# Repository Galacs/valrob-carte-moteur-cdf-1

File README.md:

# Carte moteur CDF 1

ESP32-S3-WROOM-1 Dual 5A DC motor driver

## IC List

- ESP32-S3-WROOM-1 (Main MCU Module)
- AP2112K (MCU 3v3 LDO)
- DRV8874 (Integrated FETs H-bridge)

## Top preview

## Preview 3d render

## Pin definitions

```c
#define EN_1_PIN 2
#define PH_1_PIN 3
#define SLEEP_1_PIN 5
#define FAULT_1_PIN 6
#define IPROPRI_1_PIN 7

#define EN_2_PIN 14
#define PH_2_PIN 17
#define SLEEP_2_PIN 21
#define FAULT_2_PIN 38
#define IPROPRI_2_PIN 18

#define SPI_CS_0_PIN 10
#define SPI_CS_1_PIN 8
#define SPI_MOSI_PIN 11
#define SPI_MISO_PIN 13
#define SPI_SCLK_PIN 12

#define ALERT_1_PIN 47
#define ALERT_2_PIN 48

#define BATT_SENSE_PIN 9
```

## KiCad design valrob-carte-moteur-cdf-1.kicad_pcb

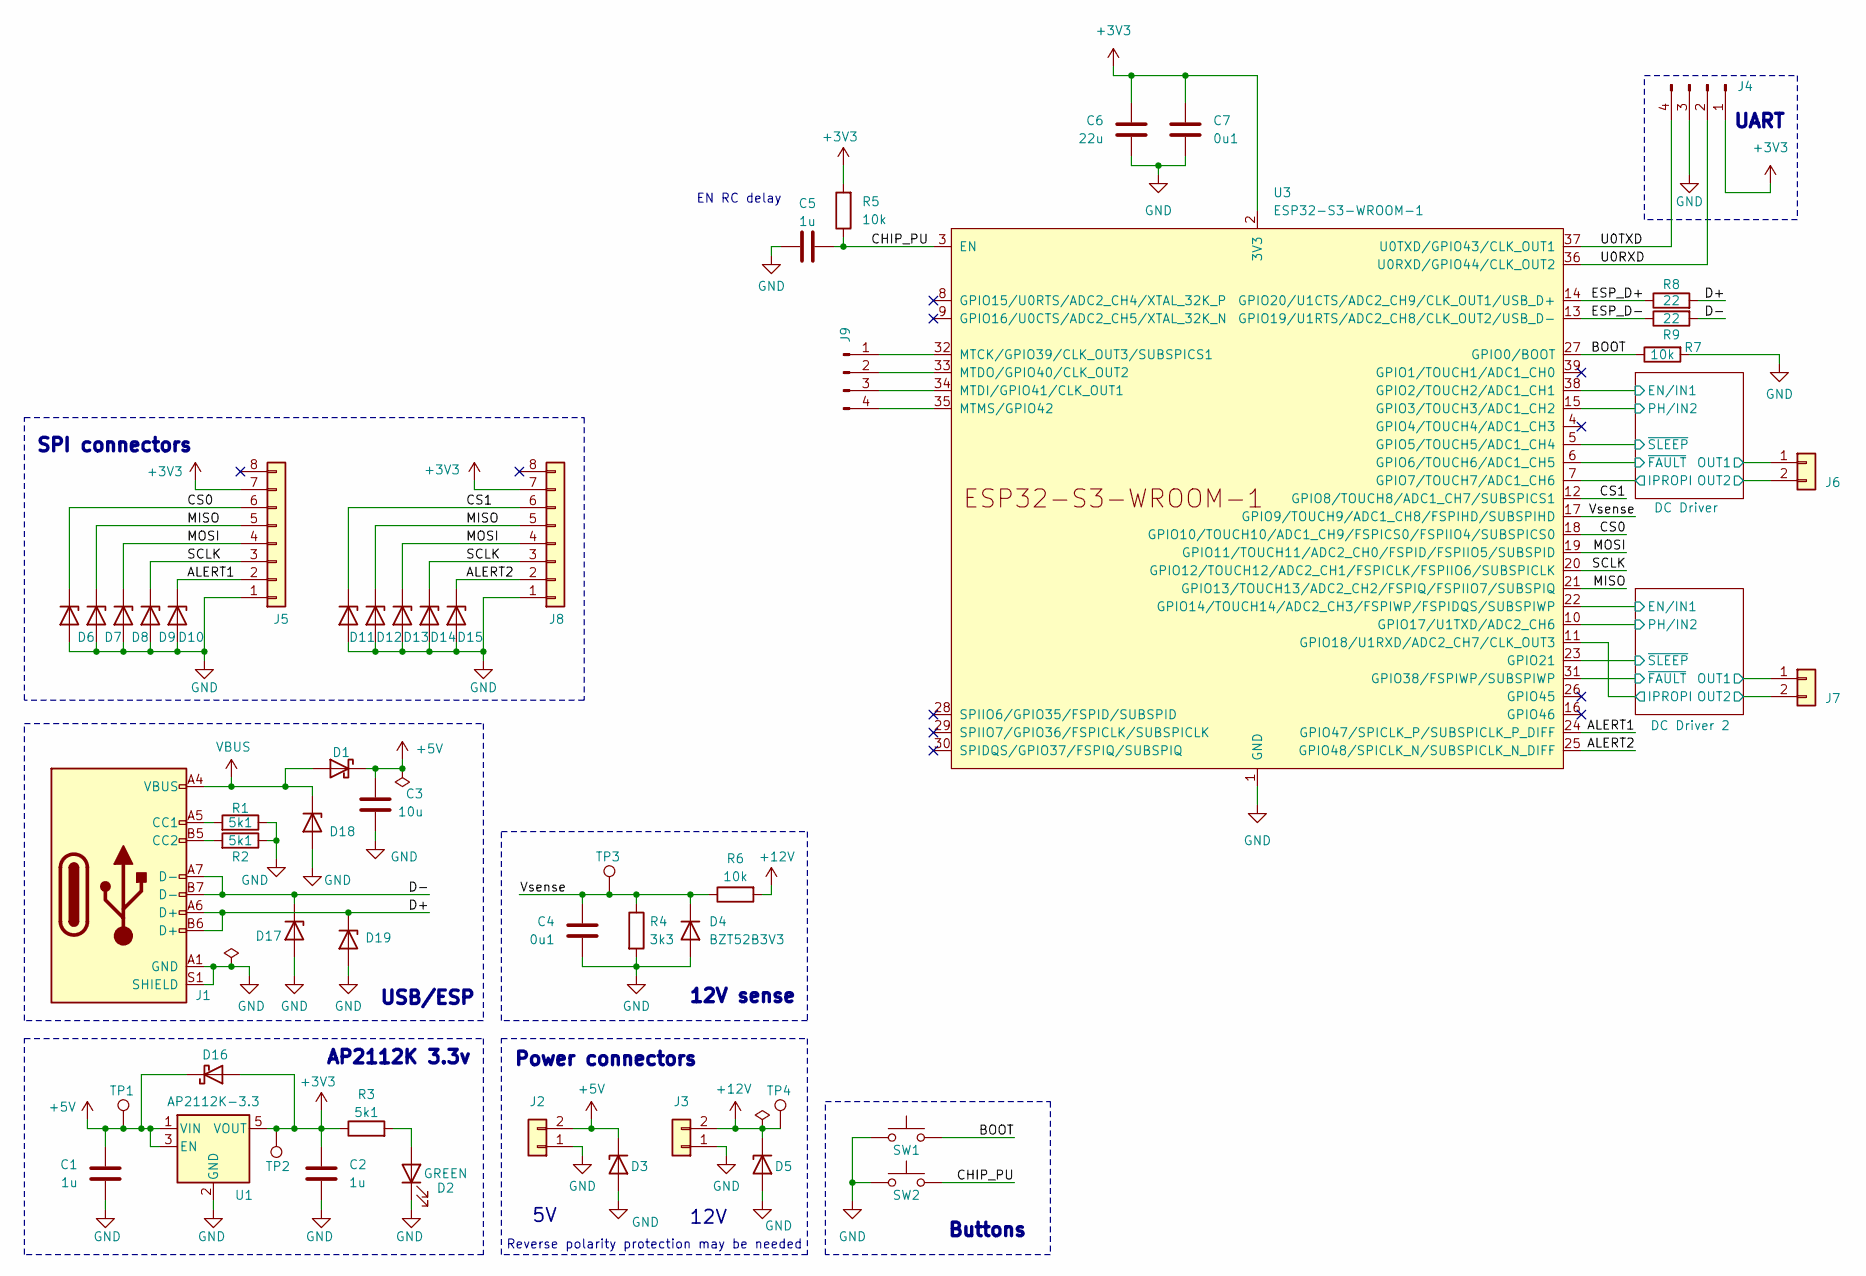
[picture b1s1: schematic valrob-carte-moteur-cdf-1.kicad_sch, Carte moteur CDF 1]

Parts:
C1, C2, C5: 1u; C_0603_1608Metric; Manufacturer Part Number CL10A105KB8NNNC; JLCPCB Part # C15849
C3: 10u; C_0603_1608Metric; Manufacturer Part Number CL10A106KP8NNNC; JLCPCB Part # C19702
C4, C7: 0u1; C_0603_1608Metric; Manufacturer Part Number CC0603KRX7R9BB104; JLCPCB Part # C14663
C6: 22u; C_0805_2012Metric; Manufacturer Part Number CL21A226MAQNNNE; JLCPCB Part # C45783
D1, D16: D_Schottky; D_SMA; Manufacturer Part Number SS54; JLCPCB Part # C22452
D2: GREEN; LED_0805_2012Metric; Manufacturer Part Number KT-0805G; JLCPCB Part # C2297
D3: P6SMB6.8CA/TR13; D_SMB; Manufacturer Part Number P6SMB6.8CA/TR13; JLCPCB Part # C78395
D4: BZT52B3V3; D_SOD-123; Manufacturer Part Number BZT52B3V3; JLCPCB Part # C19077392
D5: SMAJ12A; D_SMA; Manufacturer Part Number SMAJ12A; JLCPCB Part # C19077531
D6, D7, D8, D9, D10, D11, D12, D13, D14, D15, D17, D18, D19: H5VU10U; Diode_DFN1006; Manufacturer Part Number H5VU10U; JLCPCB Part # C22395519
J1: USB_C_Receptacle_USB2.0_14P; USB_C_Receptacle_HRO_TYPE-C-31-M-12; Manufacturer Part Number TYPE-C16PIN; JLCPCB Part # C393939
J2, J3, J6, J7: Conn_01x02; JST_XH_S2B-XH-A_1x02_P2.50mm_Horizontal
J4, J9: Conn_01x04_Pin; PinHeader_1x04_P2.54mm_Vertical
J5, J8: Conn_01x08; Molex_PicoBlade_53048-0810_1x08_P1.25mm_Horizontal
R1, R2, R3: 5k1; R_0603_1608Metric; Manufacturer Part Number 0603WAF5101T5E; JLCPCB Part # C23186
R4: 3k3; R_0603_1608Metric; Manufacturer Part Number 0603WAF3301T5E; JLCPCB Part # C22978
R5, R6, R7: 10k; R_0603_1608Metric; Manufacturer Part Number 0603WAF1002T5E; JLCPCB Part # C25804
R8, R9: 22; R_0603_1608Metric; Manufacturer Part Number 0603WAF220JT5E; JLCPCB Part # C23345
SW1, SW2: SW_Push; SW_SPST_TS-1088-xR020; Manufacturer Part Number TS-1088-AR02016; JLCPCB Part # C720477
TP1, TP2, TP3, TP4: TestPoint; TestPoint_Pad_D2.0mm
U1: AP2112K-3.3; SOT-23-5; Manufacturer Part Number AP2112K-3.3TRG1; JLCPCB Part # C51118
U3: ESP32-S3-WROOM-1

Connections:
+3V3: C2.1, C6.1, C7.1, D16.2 (A), J4.1, J5.7, J8.7, R3.1, R5.2, TP2.1, U1.5 (VOUT), U3.2 (3V3); also elsewhere on the board
+5V: C1.1, C3.1, D1.1 (K), D3.1 (K), D16.1 (K), J2.2, TP1.1, U1.1 (VIN), U1.3 (EN)
+12V: D5.1 (K), J3.2, R6.2, TP4.1; also elsewhere on the board
/ALERT1: D10.1 (K), J5.2, U3.24 (GPIO47/SPICLK_P/SUBSPICLK_P_DIFF)
/ALERT2: D15.1 (K), J8.2, U3.25 (GPIO48/SPICLK_N/SUBSPICLK_N_DIFF)
/BOOT: R7.1, SW1.2, U3.27 (GPIO0/BOOT)
/CHIP_PU: C5.2, R5.1, SW2.2, U3.3 (EN)
/CS0: D6.1 (K), J5.6, U3.18 (GPIO10/TOUCH10/ADC1_CH9/FSPICS0/FSPIIO4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)
/CS1: D11.1 (K), J8.6, U3.12 (GPIO8/TOUCH8/ADC1_CH7/SUBSPICS1)
/D+: D19.1 (K), J1.A6 (D+), J1.B6 (D+), R8.2
/D-: D17.1 (K), J1.A7 (D-), J1.B7 (D-), R9.2
/DC Driver 2/EN/IN1: U3.22 (GPIO14/TOUCH14/ADC2_CH3/FSPIWP/FSPIDQS/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); also elsewhere on the board
/DC Driver 2/IPROPI: U3.11 (GPIO18/U1RXD/ADC2_CH7/CLK_OUT3); also elsewhere on the board
/DC Driver 2/OUT1: J7.1; also elsewhere on the board
/DC Driver 2/OUT2: J7.2; also elsewhere on the board
/DC Driver 2/PH/IN2: U3.10 (GPIO17/U1TXD/ADC2_CH6); also elsewhere on the board
/DC Driver 2/~FAULT: U3.31 (GPIO38/FSPIWP/SUBSPIWP); also elsewhere on the board
/DC Driver 2/~SLEEP: U3.23 (GPIO21); also elsewhere on the board
/DC Driver/EN/IN1: U3.38 (GPIO2/TOUCH2/ADC1_CH1); also elsewhere on the board
/DC Driver/IPROPI: U3.7 (GPIO7/TOUCH7/ADC1_CH6); also elsewhere on the board
/DC Driver/OUT1: J6.1; also elsewhere on the board
/DC Driver/OUT2: J6.2; also elsewhere on the board
/DC Driver/PH/IN2: U3.15 (GPIO3/TOUCH3/ADC1_CH2); also elsewhere on the board
/DC Driver/~FAULT: U3.6 (GPIO6/TOUCH6/ADC1_CH5); also elsewhere on the board
/DC Driver/~SLEEP: U3.5 (GPIO5/TOUCH5/ADC1_CH4); also elsewhere on the board
/ESP_D+: R8.1, U3.14 (GPIO20/U1CTS/ADC2_CH9/CLK_OUT1/USB_D+)
/ESP_D-: R9.1, U3.13 (GPIO19/U1RTS/ADC2_CH8/CLK_OUT2/USB_D-)
/MISO: D7.1 (K), D12.1 (K), J5.5, J8.5, U3.21 (GPIO13/TOUCH13/ADC2_CH2/FSPIQ/FSPIIO7/S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)
/MOSI: D8.1 (K), D13.1 (K), J5.4, J8.4, U3.19 (GPIO11/TOUCH11/ADC2_CH0/FSPID/FSPIIO5/S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)
/SCLK: D9.1 (K), D14.1 (K), J5.3, J8.3, U3.20 (GPIO12/TOUCH12/ADC2_CH1/FSPICLK/FSPIIO6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)
/U0RXD: J4.2, U3.36 (U0RXD/GPIO44/CLK_OUT2)
/U0TXD: J4.4, U3.37 (U0TXD/GPIO43/CLK_OUT1)
/Vsense: C4.1, D4.1 (K), R4.1, R6.1, TP3.1, U3.17 (GPIO9/TOUCH9/ADC1_CH8/FSPIHD/SUBSPIHD)
GND: C1.2, C2.2, C3.2, C4.2, C5.1, C6.2, C7.2, D2.1 (K), D3.2 (A), D4.2 (A), D5.2 (A), D6.2 (A), D7.2 (A), D8.2 (A), D9.2 (A), D10.2 (A), D11.2 (A), D12.2 (A), D13.2 (A), D14.2 (A), D15.2 (A), D17.2 (A), D18.2 (A), D19.2 (A), J1.A1 (GND), J1.A12 (GND), J1.B1 (GND), J1.B12 (GND), J1.S1 (SHIELD), J2.1, J3.1, J4.3, J5.1, J8.1, R1.1, R2.1, R4.2, R7.2, SW1.1, SW2.1, U1.2 (GND), U3.1 (GND), U3.40 (GND), U3.41 (GND); also elsewhere on the board
unnamed: D2.2 (A), R3.2
unnamed: J1.A5 (CC1), R1.2
unnamed: J1.B5 (CC2), R2.2
unnamed: J9.1, U3.32 (MTCK/GPIO39/CLK_OUT3/SUBSPICS1)
unnamed: J9.2, U3.33 (MTDO/GPIO40/CLK_OUT2)
unnamed: J9.3, U3.34 (MTDI/GPIO41/CLK_OUT1)
unnamed: J9.4, U3.35 (MTMS/GPIO42)
VBUS: D1.2 (A), D18.1 (K), J1.A4 (VBUS), J1.A9 (VBUS), J1.B4 (VBUS), J1.B9 (VBUS)

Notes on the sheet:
SPI connectors
12V sense
Power connectors
Reverse polarity protection may be needed
AP2112K 3.3v
USB/ESP
Buttons
12V
UART
EN RC delay

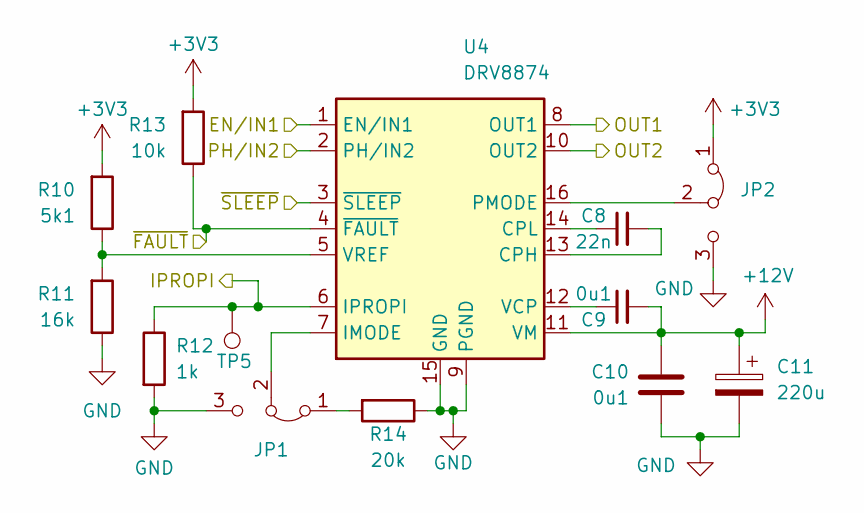
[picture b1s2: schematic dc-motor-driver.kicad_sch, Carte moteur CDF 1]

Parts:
C8: 22n; C_0603_1608Metric; Manufacturer Part Number CL10B223KB8NNNC; JLCPCB Part # C21122
C9, C10: 0u1; C_0603_1608Metric; Manufacturer Part Number CC0603KRX7R9BB104; JLCPCB Part # C14663
C11: 220u; CP_Elec_6.3x7.7; Manufacturer Part Number JVJ35V220M6x8; JLCPCB Part # C46550411
JP1, JP2: Jumper_3_Bridged12; PinHeader_1x03_P2.54mm_Vertical
R10: 5k1; R_0603_1608Metric; Manufacturer Part Number 0603WAF5101T5E; JLCPCB Part # C23186
R11: 16k; R_0805_2012Metric; Manufacturer Part Number 0805W8F1602T5E; JLCPCB Part # C17490
R12: 1k; R_0603_1608Metric; Manufacturer Part Number 0603WAF1001T5E; JLCPCB Part # C21190
R13: 10k; R_0603_1608Metric; Manufacturer Part Number 0603WAF1002T5E; JLCPCB Part # C25804
R14: 20k; R_0603_1608Metric; Manufacturer Part Number 0603WAF2002T5E; JLCPCB Part # C4184
TP5: TestPoint; TestPoint_Pad_D2.0mm
U4: DRV8874; HTSSOP-16-1EP_4.4x5mm_P0.65mm_EP3.4x5mm_Mask2.46x2.31mm_The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; Manufacturer Part Number DRV8874PWPR; JLCPCB Part # C1855818

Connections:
+3V3: JP2.1 (A), R10.2, R13.2; also elsewhere on the board
+12V: C9.2, C10.1, C11.1, U4.11 (VM); also elsewhere on the board
/DC Driver/EN/IN1: U4.1 (EN/IN1); also elsewhere on the board
/DC Driver/IPROPI: R12.1, TP5.1, U4.6 (IPROPI); also elsewhere on the board
/DC Driver/OUT1: U4.8 (OUT1); also elsewhere on the board
/DC Driver/OUT2: U4.10 (OUT2); also elsewhere on the board
/DC Driver/PH/IN2: U4.2 (PH/IN2); also elsewhere on the board
/DC Driver/~FAULT: R13.1, U4.4 (~FAULT); also elsewhere on the board
/DC Driver/~SLEEP: U4.3 (~SLEEP); also elsewhere on the board
GND: C10.2, C11.2, JP1.3 (B), JP2.3 (B), R11.1, R12.2, R14.1, U4.9 (PGND), U4.15 (GND); also elsewhere on the board
unnamed: JP1.1 (A), R14.2
unnamed: JP1.2 (C), U4.7 (IMODE)
unnamed: JP2.2 (C), U4.16 (PMODE)
unnamed: C8.2, U4.13 (CPH)
unnamed: C8.1, U4.14 (CPL)
unnamed: C9.1, U4.12 (VCP)
unnamed: R10.1, R11.2, U4.5 (VREF)

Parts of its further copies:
C12: 22n; C_0603_1608Metric; Manufacturer Part Number CL10B223KB8NNNC; JLCPCB Part # C21122
C13, C14: 0u1; C_0603_1608Metric; Manufacturer Part Number CC0603KRX7R9BB104; JLCPCB Part # C14663
C15: 220u; CP_Elec_6.3x7.7; Manufacturer Part Number JVJ35V220M6x8; JLCPCB Part # C46550411
JP3, JP4: Jumper_3_Bridged12; PinHeader_1x03_P2.54mm_Vertical
R15: 5k1; R_0603_1608Metric; Manufacturer Part Number 0603WAF5101T5E; JLCPCB Part # C23186
R16: 16k; R_0805_2012Metric; Manufacturer Part Number 0805W8F1602T5E; JLCPCB Part # C17490
R17: 1k; R_0603_1608Metric; Manufacturer Part Number 0603WAF1001T5E; JLCPCB Part # C21190
R18: 10k; R_0603_1608Metric; Manufacturer Part Number 0603WAF1002T5E; JLCPCB Part # C25804
R19: 20k; R_0603_1608Metric; Manufacturer Part Number 0603WAF2002T5E; JLCPCB Part # C4184
TP6: TestPoint; TestPoint_Pad_D2.0mm
U5: DRV8874; HTSSOP-16-1EP_4.4x5mm_P0.65mm_EP3.4x5mm_Mask2.46x2.31mm_The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; Manufacturer Part Number DRV8874PWPR; JLCPCB Part # C1855818

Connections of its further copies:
+3V3: JP4.1 (A), R15.2, R18.2; also elsewhere on the board
+12V: C13.2, C14.1, C15.1, U5.11 (VM); also elsewhere on the board
/DC Driver 2/EN/IN1: U5.1 (EN/IN1); also elsewhere on the board
/DC Driver 2/IPROPI: R17.1, TP6.1, U5.6 (IPROPI); also elsewhere on the board
/DC Driver 2/OUT1: U5.8 (OUT1); also elsewhere on the board
/DC Driver 2/OUT2: U5.10 (OUT2); also elsewhere on the board
/DC Driver 2/PH/IN2: U5.2 (PH/IN2); also elsewhere on the board
/DC Driver 2/~FAULT: R18.1, U5.4 (~FAULT); also elsewhere on the board
/DC Driver 2/~SLEEP: U5.3 (~SLEEP); also elsewhere on the board
GND: C14.2, C15.2, JP3.3 (B), JP4.3 (B), R16.1, R17.2, R19.1, U5.9 (PGND), U5.15 (GND); also elsewhere on the board
unnamed: JP3.1 (A), R19.2
unnamed: JP3.2 (C), U5.7 (IMODE)
unnamed: JP4.2 (C), U5.16 (PMODE)
unnamed: C12.2, U5.13 (CPH)
unnamed: C12.1, U5.14 (CPL)
unnamed: C13.1, U5.12 (VCP)
unnamed: R15.1, R16.2, U5.5 (VREF)

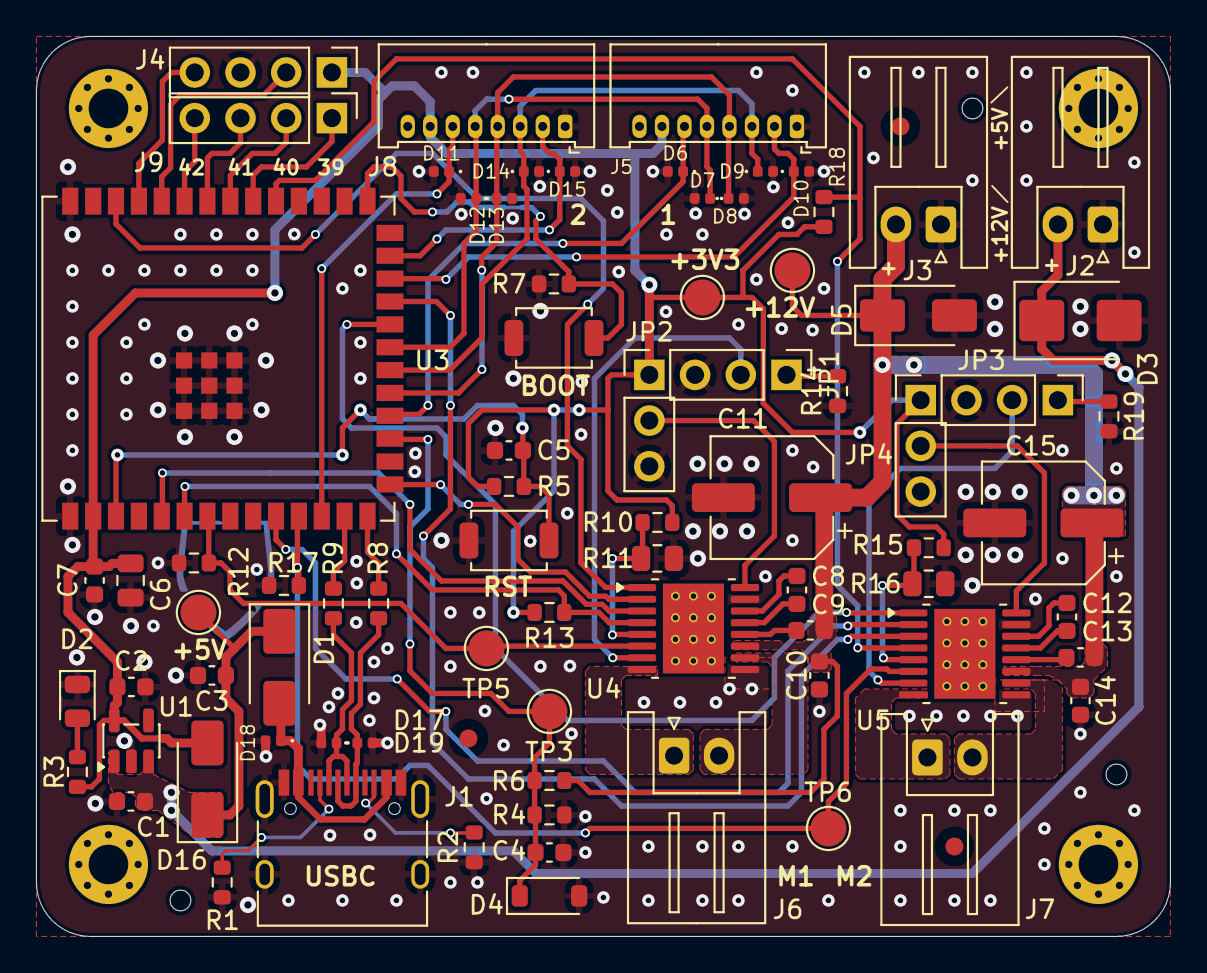
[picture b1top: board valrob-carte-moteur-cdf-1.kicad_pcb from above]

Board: 2 copper layers, 63.0 x 50.0 mm, 78 parts (0 on the bottom side), 56 nets.

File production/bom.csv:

Designator,Footprint,Quantity,Value,LCSC Part #
"_2, ",,2,,
"C1, C2, C5",0603,3,1u,C15849
"C10, C13, C14, C4, C7, C9",0603,6,0u1,C14663
"C11, C15",CP_Elec_6.3x7.7,2,220u,C46550411
"C12, C8",0603,2,22n,C21122
C3,0603,1,10u,C19702
C6,0805,1,22u,C45783
"D1, D16",D_SMA,2,D_Schottky,C22452
"D10, D11, D12, D13, D14, D15, D17, D18, D19, D6, D7, D8, D9",Diode_DFN1006,13,H5VU10U,C22395519
D2,0805,1,GREEN,C2297
D3,D_SMB,1,P6SMB6.8CA/TR13,C78395
D4,D_SOD-123,1,BZT52B3V3,C19077392
D5,D_SMA,1,SMAJ12A,C19077531
J1,USB_C_Receptacle_HRO_TYPE-C-31-M-12,1,USB_C_Receptacle_USB2.0_14P,C393939
"R1, R10, R15, R2, R3",0603,5,5k1,C23186
"R11, R16",0805,2,16k,C17490
"R12, R17",0603,2,1k,C21190
"R13, R18, R5, R6, R7",0603,5,10k,C25804
"R14, R19",0603,2,20k,C4184
R4,0603,1,3k3,C22978
"R8, R9",0603,2,22,C23345
"SW1, SW2",SW_SPST_TS-1088-xR020,2,SW_Push,C720477
U1,SOT-23-5,1,AP2112K-3.3,C51118
"U4, U5",HTSSOP-16-1EP_4.4x5mm_P0.65mm_EP3.4x5mm_Mask2.46x2.31mm_ThermalVias,2,DRV8874,C1855818

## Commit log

2025-11-23 schem: add ESP32-S3-WROOM-1 symbol
2025-11-23 schem: add ESP32 decoupling caps
2025-11-23 schem: import AP2112K 3.3v from esp32c6-sensor-devboard
2025-11-23 schem: import USB-C from esp32c6-sensor-devboard
2025-11-23 schem: add BOOT and CHIP_PU strapping pullups
2025-11-23 schem: import boot and rst btns from esp32c6-sensor-devboard
2025-11-23 schem: import UART connector without series resistor from esp32c6-sensor-devboard
2025-11-23 schem: add USB termination resistors
2025-11-23 schem: add power 5v and 12v power input connectors
2025-11-23 schem: add 12v sense from MCU ADC or GPIO
2025-11-23 schem: add ESD/Surge protection to power inputs
2025-11-23 schem: add SPI connectors
2025-11-23 schem: add DRV8874 dc motor driver
2025-11-23 schem: add second dc motor driver
2025-11-23 schem: connect SPI connectors to ESP32S3
2025-11-23 schem: add various test points
2025-11-23 schem: add no connects to unused ESP32 pins
2025-11-23 schem: add net classes
2025-11-23 schem: connect alert pins to ESP32
2025-11-23 schem: reannotate
2025-11-23 schem: run and fix ERC
2025-11-23 schem: add sheet titles
2025-11-23 schem: reorganize layout
2025-11-23 schem: add components footprints
2025-11-23 schem: add ordering info to BOM
2025-11-23 pcb: create file
2025-11-23 pcb: import stackup and constraints
2025-11-23 pcb: switch stackup to 2 layers
2025-11-23 pcb: import footprints from schematic
2025-11-23 pcb: add missing 3d models
2025-11-23 pcb: initial rough placement
2025-11-23 schem: update net classes assignments
2025-11-23 schem: add ldo reverse current protection diode
2025-11-23 pcb: add 4 M2 mounting holes
2025-11-23 pcb: add fiducials and tooling holes
2025-11-23 pcb: layout refinement
2025-11-23 pcb: add gnd planes
2025-11-23 pcb: add ground vias
2025-11-23 pcb: add usb routing
2025-11-23 pcb: add SPI routing
2025-11-23 pcb: add uart routing
2025-11-23 pcb: add DRV8874 dc motor driver routing
2025-11-23 pcb: add 12V routing
2025-11-23 pcb: route power
2025-11-23 pcb: add CHIP_PU AND BOOT routing
2025-11-23 pcb(silkscreen): clean reference designators
2025-11-23 pcb: add stitching vias
2025-11-23 pcb: run and fix DRC
2025-11-23 pcb: remove unused internal pads
2025-11-23 pcb: add title
2025-11-23 pcb: add silkscreen bling
2025-11-23 add spare gpios
2025-11-23 pcb(silkscreen): add JLC order number placeholder
2025-11-24 add production files
2025-11-24 pcb: add company logo to back
2025-11-24 update production files
2025-11-25 switch ST usb ESD to H5VU10U tvs diodes
2025-11-25 pcb(silkscreeen): improvements
2025-11-25 fix spi connectors TVS diodes polarity
2025-11-25 schem: fix batt sense
2025-11-30 bom: change dc driver bulk capacitors P#
2025-11-30 regenerate production files
2025-12-05 add README.md
2025-12-05 docs: add pin definitions to readme
2025-12-11 docs: add preview images to README
